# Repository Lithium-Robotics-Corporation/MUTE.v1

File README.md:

# MUTE
### Mini Universal Terminal Emulator

This is a small project I made, which is supposed to be a UART to SPI converter, meant specifically to act as a terminal emulator for SPI TFT displays.  

Features:  
- EFM8BB10F8G Silicon Labs microcontroller
- FT232RL USB 2.0 to UART bridge
- I2C, UART, GPIO, and C2D ports
- Built-in REG1117 5V to 3.3V LDO
- 2 layer PCB
- Designed for ILI9225 SPI TFT display

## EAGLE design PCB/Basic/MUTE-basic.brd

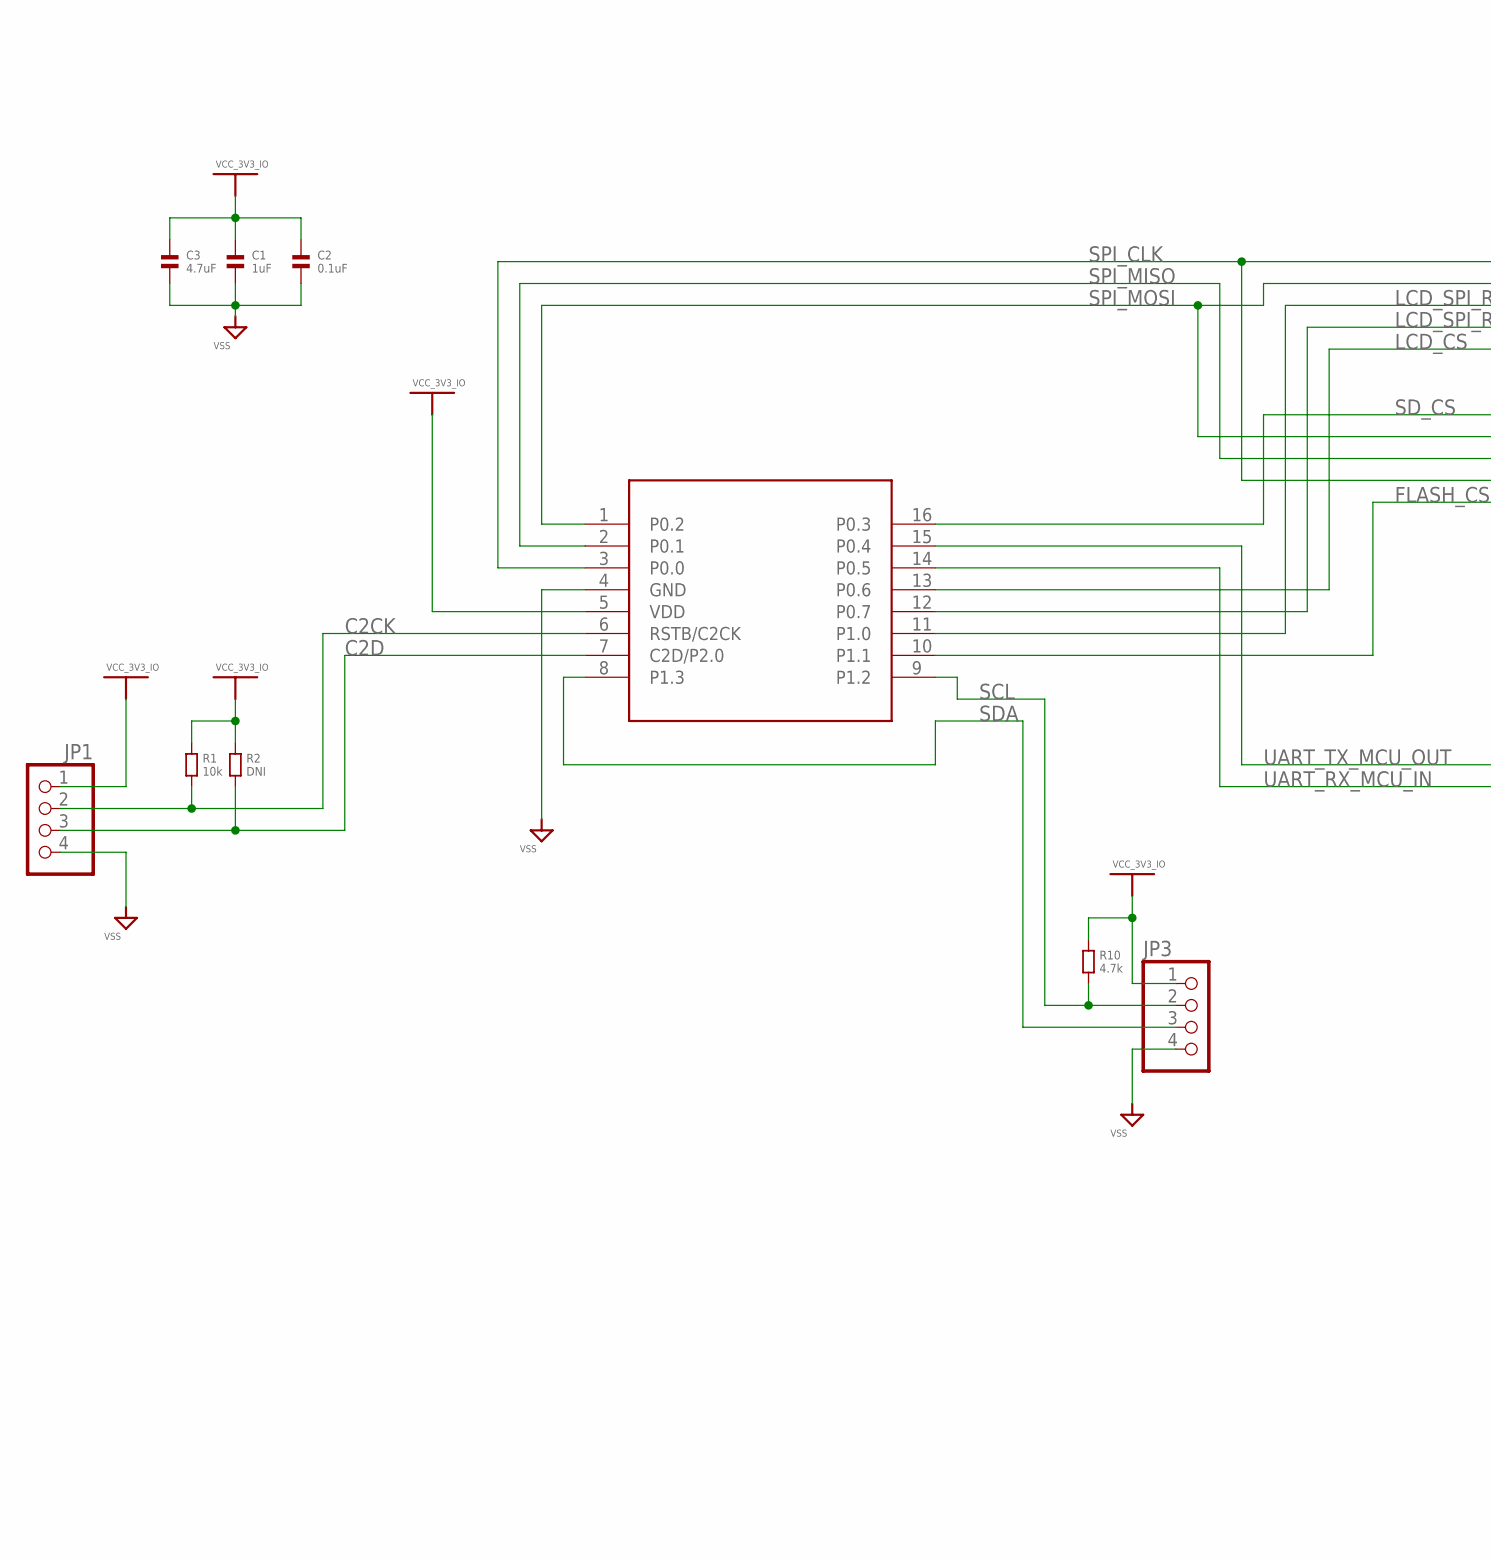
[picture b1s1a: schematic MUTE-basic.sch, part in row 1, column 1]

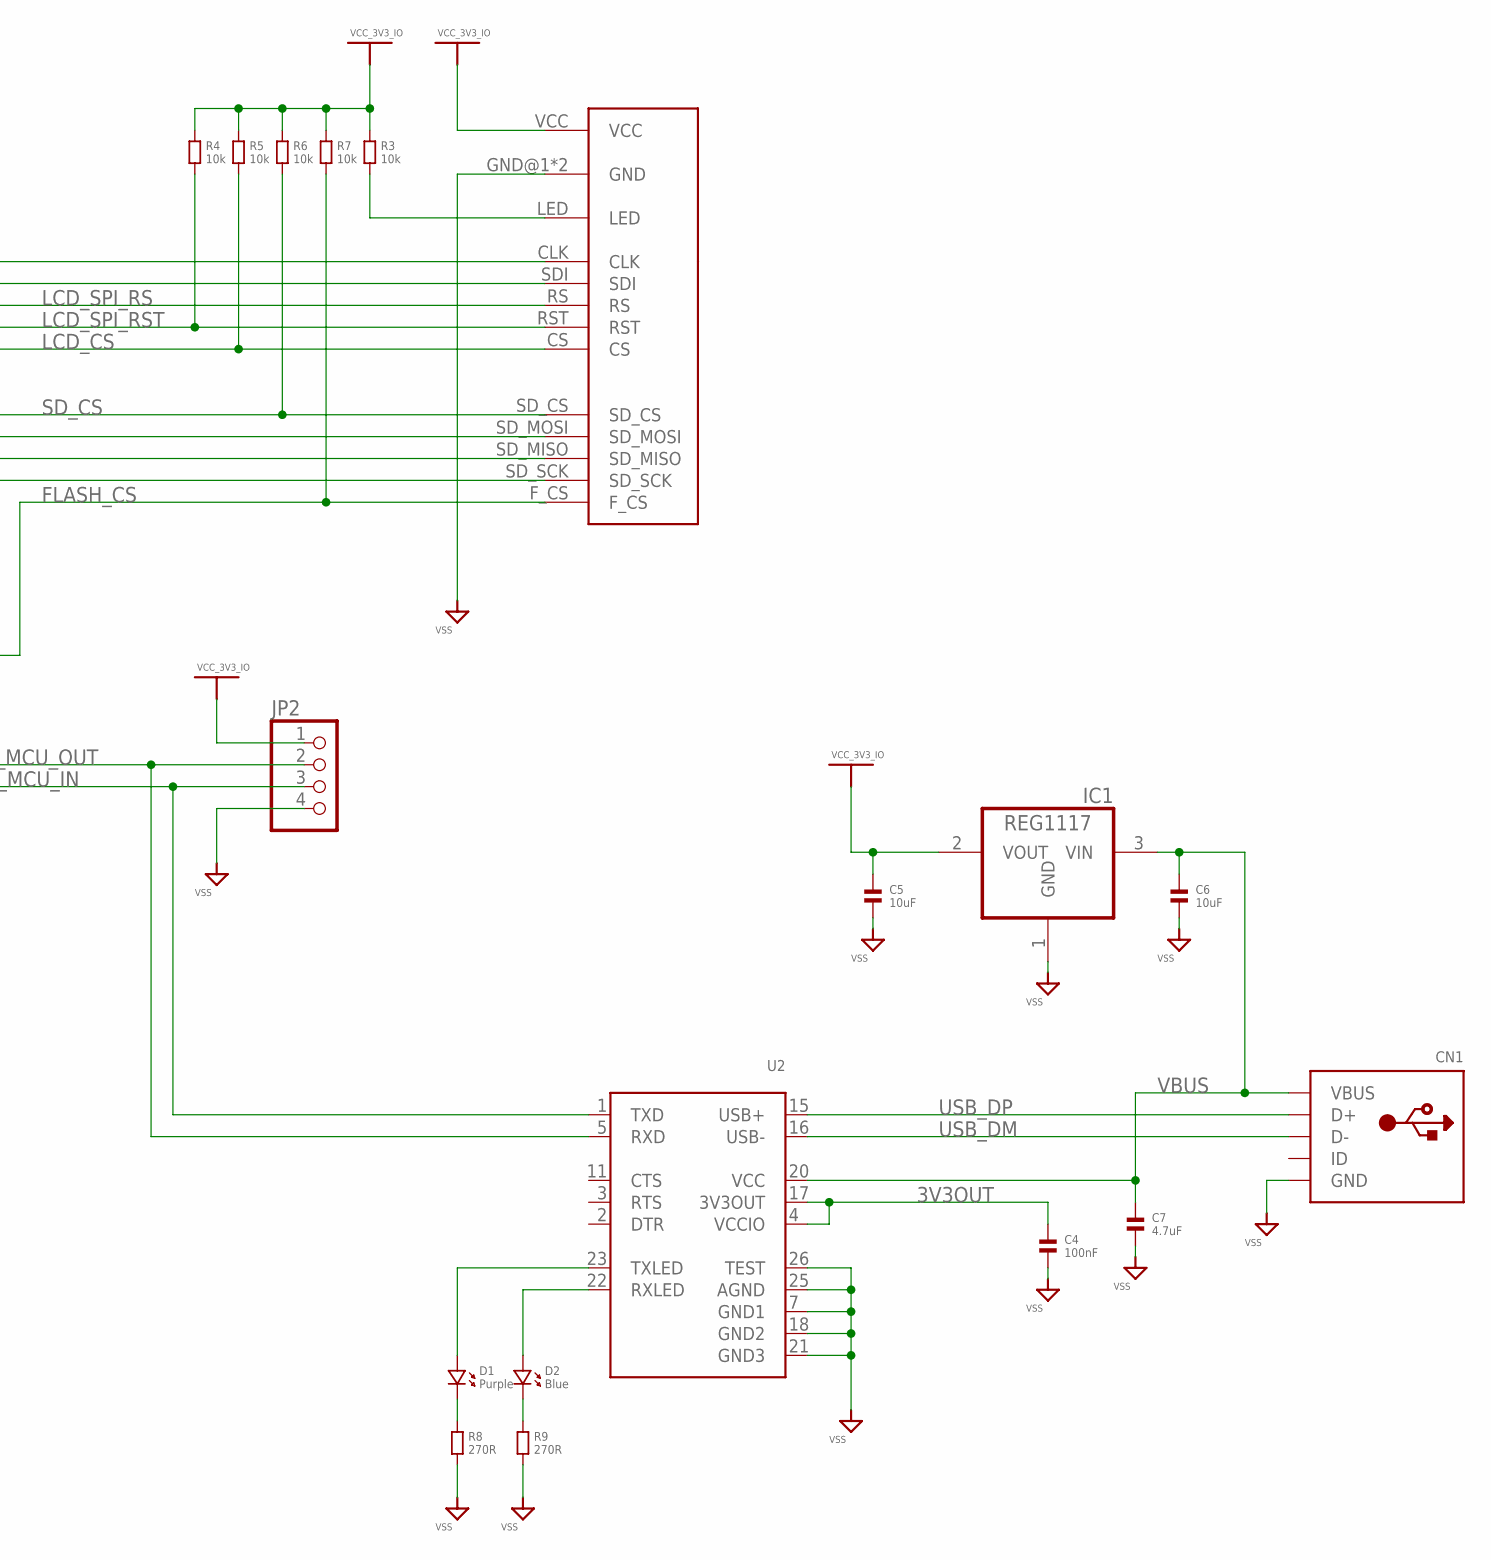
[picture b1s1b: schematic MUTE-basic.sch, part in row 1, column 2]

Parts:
C1: 1uF; 0603
C2: 0.1uF; 0603
C3, C7: 4.7uF; 0603
C4: 100nF; 0603
C5, C6: 10uF; 0603
CN1: USBMINIB; USB-MINIB
D1: Purple; 0603.LED
D2: Blue; 0603.LED
IC1: REG1117; SOT223
JP1, JP2, JP3: PINHD-1X4; 1X04
R1, R3, R4, R5, R6, R7: 10k; 0603
R2: DNI; 0603
R8, R9: 270R; 0603
R10: 4.7k; 0603
U1: SILICON_LABS-MICROCONTROLLER-EFM8BB10F8G-SOIC16; SILICON_LABS-MICROCONTROLLER-EFM8BB10F8G-A-SOIC16
U2: FT232RLSSOP28; SSOP28DB
U$1: WINGONEER_ILI9225

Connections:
3V3OUT: C4.1, U2.4 (VCCIO), U2.17 (3V3OUT)
C2CK: JP1.2, R1.2, U1.6 (RSTB/C2CK)
C2D: JP1.3, R2.2, U1.7 (C2D/P2.0)
FLASH_CS: R7.2, U1.10 (P1.1), U$1.F_CS
LCD_CS: R5.2, U1.13 (P0.6), U$1.CS
LCD_SPI_RS: U1.11 (P1.0), U$1.RS
LCD_SPI_RST: R4.2, U1.12 (P0.7), U$1.RST
unnamed: R3.2, U$1.LED
unnamed: D1.P$1 (1), U2.23 (TXLED)
unnamed: D2.P$1 (1), U2.22 (RXLED)
unnamed: D2.P$2 (2), R9.1
unnamed: D1.P$2 (2), R8.1
SCL: JP3.2, R10.2, U1.9 (P1.2)
SDA: JP3.3, U1.8 (P1.3)
SD_CS: R6.2, U1.16 (P0.3), U$1.SD_CS
SPI_CLK: U1.3 (P0.0), U$1.CLK, U$1.SD_SCK
SPI_MISO: U1.2 (P0.1), U$1.SD_MISO
SPI_MOSI: U1.1 (P0.2), U$1.SDI, U$1.SD_MOSI
UART_RX_MCU_IN: JP2.3, U1.14 (P0.5), U2.1 (TXD)
UART_TX_MCU_OUT: JP2.2, U1.15 (P0.4), U2.5 (RXD)
USB_DM: CN1.D-, U2.16 (USB-)
USB_DP: CN1.D+, U2.15 (USB+)
VBUS: C6.1, C7.1, CN1.VBUS, IC1.3 (VIN), U2.20 (VCC)
VCC_3V3_IO: C1.1, C2.1, C3.1, C5.1, IC1.2 (VOUT), JP1.1, JP2.1, JP3.1, R1.1, R2.1, R3.1, R4.1, R5.1, R6.1, R7.1, R10.1, U1.5 (VDD), U$1.VCC
VSS: C1.2, C2.2, C3.2, C4.2, C5.2, C6.2, C7.2, CN1.GND, IC1.1 (GND), JP1.4, JP2.4, JP3.4, R8.2, R9.2, U1.4 (GND), U2.7 (GND1), U2.18 (GND2), U2.21 (GND3), U2.25 (AGND), U2.26 (TEST), U$1.GND@1 (GND), U$1.GND@2 (GND)

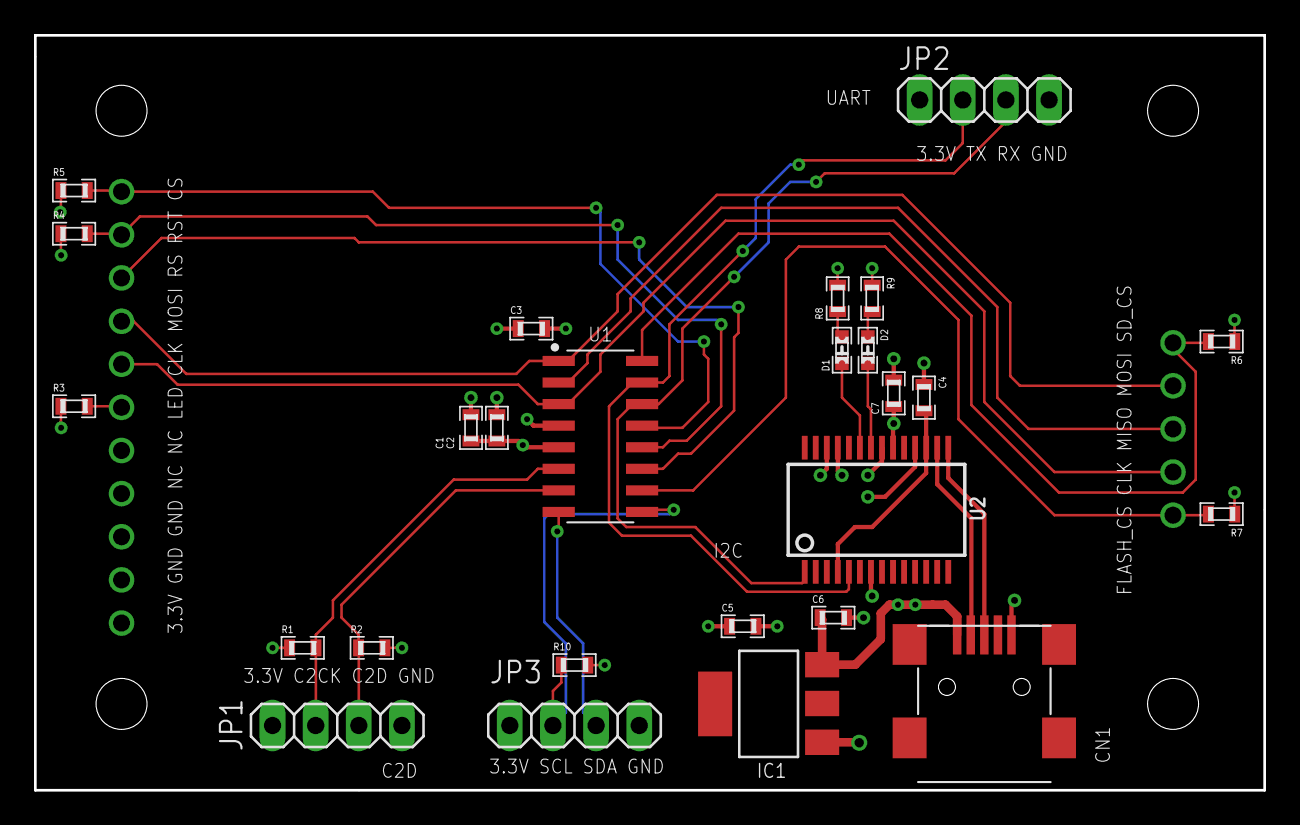
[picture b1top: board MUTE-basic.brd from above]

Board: 2 copper layers, 72.4 x 44.4 mm, 27 parts (0 on the bottom side), 25 nets.

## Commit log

2020-11-29 Designed system. Initial upload
2020-11-29 Added silkscreen annotations
2020-11-29 Updated MCU to SOIC16 version for availability
2020-12-05 Added some code to drive ILI9225

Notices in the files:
parts and their libraries:
microbuilder: This work is placed in the public domain, and may be freely used for commercial and non-commercial work with the following conditions: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
